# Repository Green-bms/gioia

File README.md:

# Gioia - glittering fashion
Electronic wearable device <br> 
<br> 

Youtube: https://youtu.be/MnyeiMZdmjQ?si=YpLxnYz4cA8ocs8j <br> 
Instructables: https://www.instructables.com/Gioia-Glittering-Fashion/ <br> 
Hackaday.io: https://hackaday.io/project/202226-gioia-glittering-fashion <br> 
Hackster.io: https://www.hackster.io/green-bms/gioia-glittering-fashion-81f5f8 <br> 
Purchase PCB here: <br> 
https://www.pcbway.com/project/shareproject/Gioia_glittering_fashion_21_monocrome_leds_caeb9192.html  <br>
https://www.pcbway.com/project/shareproject/Gioia_glittering_fashion_8_RGB_leds_abd15673.html <br>

## Description
"Gioia" in Italian means joy.<br> 
I wanted to call this project this way in the hope that it will bring joy and happiness to those who wear it.<br> 
This gadget of 3 cm of diametrer can contain a maximum of 24 single-color LEDs or 8 RGB LEDs.<br> 
The infinite animations, which also include letters and symbols, are managed by an Attiny85 microcontroller.<br> 

### The PCB
Gioia's PCBs are made by PCBway https://pcbway.com/g/kY6w10 <br>
 <br>
I chose this supplier because the quality of the PCB and the assembly of the components is of great quality.
The assistance is excellent and the delivery times are always respected <br>
 <br>

### Battery
The device is powered by a 30mAh LIR1632 rechargeable lithium battery. <br>
 <br> 
Charging is done via a micro USB connector and takes about 90 minutes from 0% to 100%
The device lasts for about 5 continuous hours

### Versions
The project is available in 2 versions:<br>

#### 21 monochrome leds:<br>
 <br> 
All the documentation to make it is available here: https://github.com/Green-bms/gioia/tree/master/21%20monochrome%20leds%20version

#### 8 RGB leds:<br>
 <br> 
Each LED can light up in one of these 7 colors: red, green, blue, yellow, fuchsia, aqua, white. <br>
All the documentation to make it is available here: https://github.com/Green-bms/gioia/tree/master/8%20RGB%20leds%20version

### Microcontroller
The device's LEDs are driven by an Attiny85 microcontroller and 3 74HC595 shift registers.<br> 
The LED animations that can compose various light games, texts and symbols, are programmed in the code to be loaded into the microcontroller<br> 
Programming the microcontroller is very simple: you need to power the device via USB and connect the 4 pins of the ISP programmer to the pads shown in the pictures below.<br> 

## Open source Development applications
The project was created using the following Open source applications:
- **KiCad** : to design pcb
- **Arduino IDE** : to design the code for Attiny85 microcontroller of device animations

## Warning
This project is not commercial. This project is for educational and technological purposes.
No warrenty is foreseen.
Green BMS assumes no responsibility for any errors or inaccuracies that may appear in any documentation or file or any software that may be provided.
The use of this project is done entirely at your own risk and responsibility.
The use of this project may not be compliant with local laws or regulations.

## License

This work is licensed under a **Creative Commons Attribution-ShareAlike 4.0 International License**.
https://creativecommons.org/licenses/by-sa/4.0/

### You are free to:

**Share** — copy and redistribute the material in any medium or format

**Adapt**  — remix, transform, and build upon the material
for any purpose, even commercially.
This license is acceptable for Free Cultural Works.
The licensor cannot revoke these freedoms as long as you follow the license terms.

### Under the following terms:

**Attribution** — You must give appropriate credit, provide a link to the license, and indicate if changes were made. You may do so in any reasonable manner, but not in any way that suggests the licensor endorses you or your use.

**ShareAlike** — If you remix, transform, or build upon the material, you must distribute your contributions under the same license as the original.

**No additional restrictions** — You may not apply legal terms or technological measures that legally restrict others from doing anything the license permits.

### Notices:
You do not have to comply with the license for elements of the material in the public domain or where your use is permitted by an applicable exception or limitation.
No warranties are given. The license may not give you all of the permissions necessary for your intended use. For example, other rights such as publicity, privacy, or moral rights may limit how you use the material.

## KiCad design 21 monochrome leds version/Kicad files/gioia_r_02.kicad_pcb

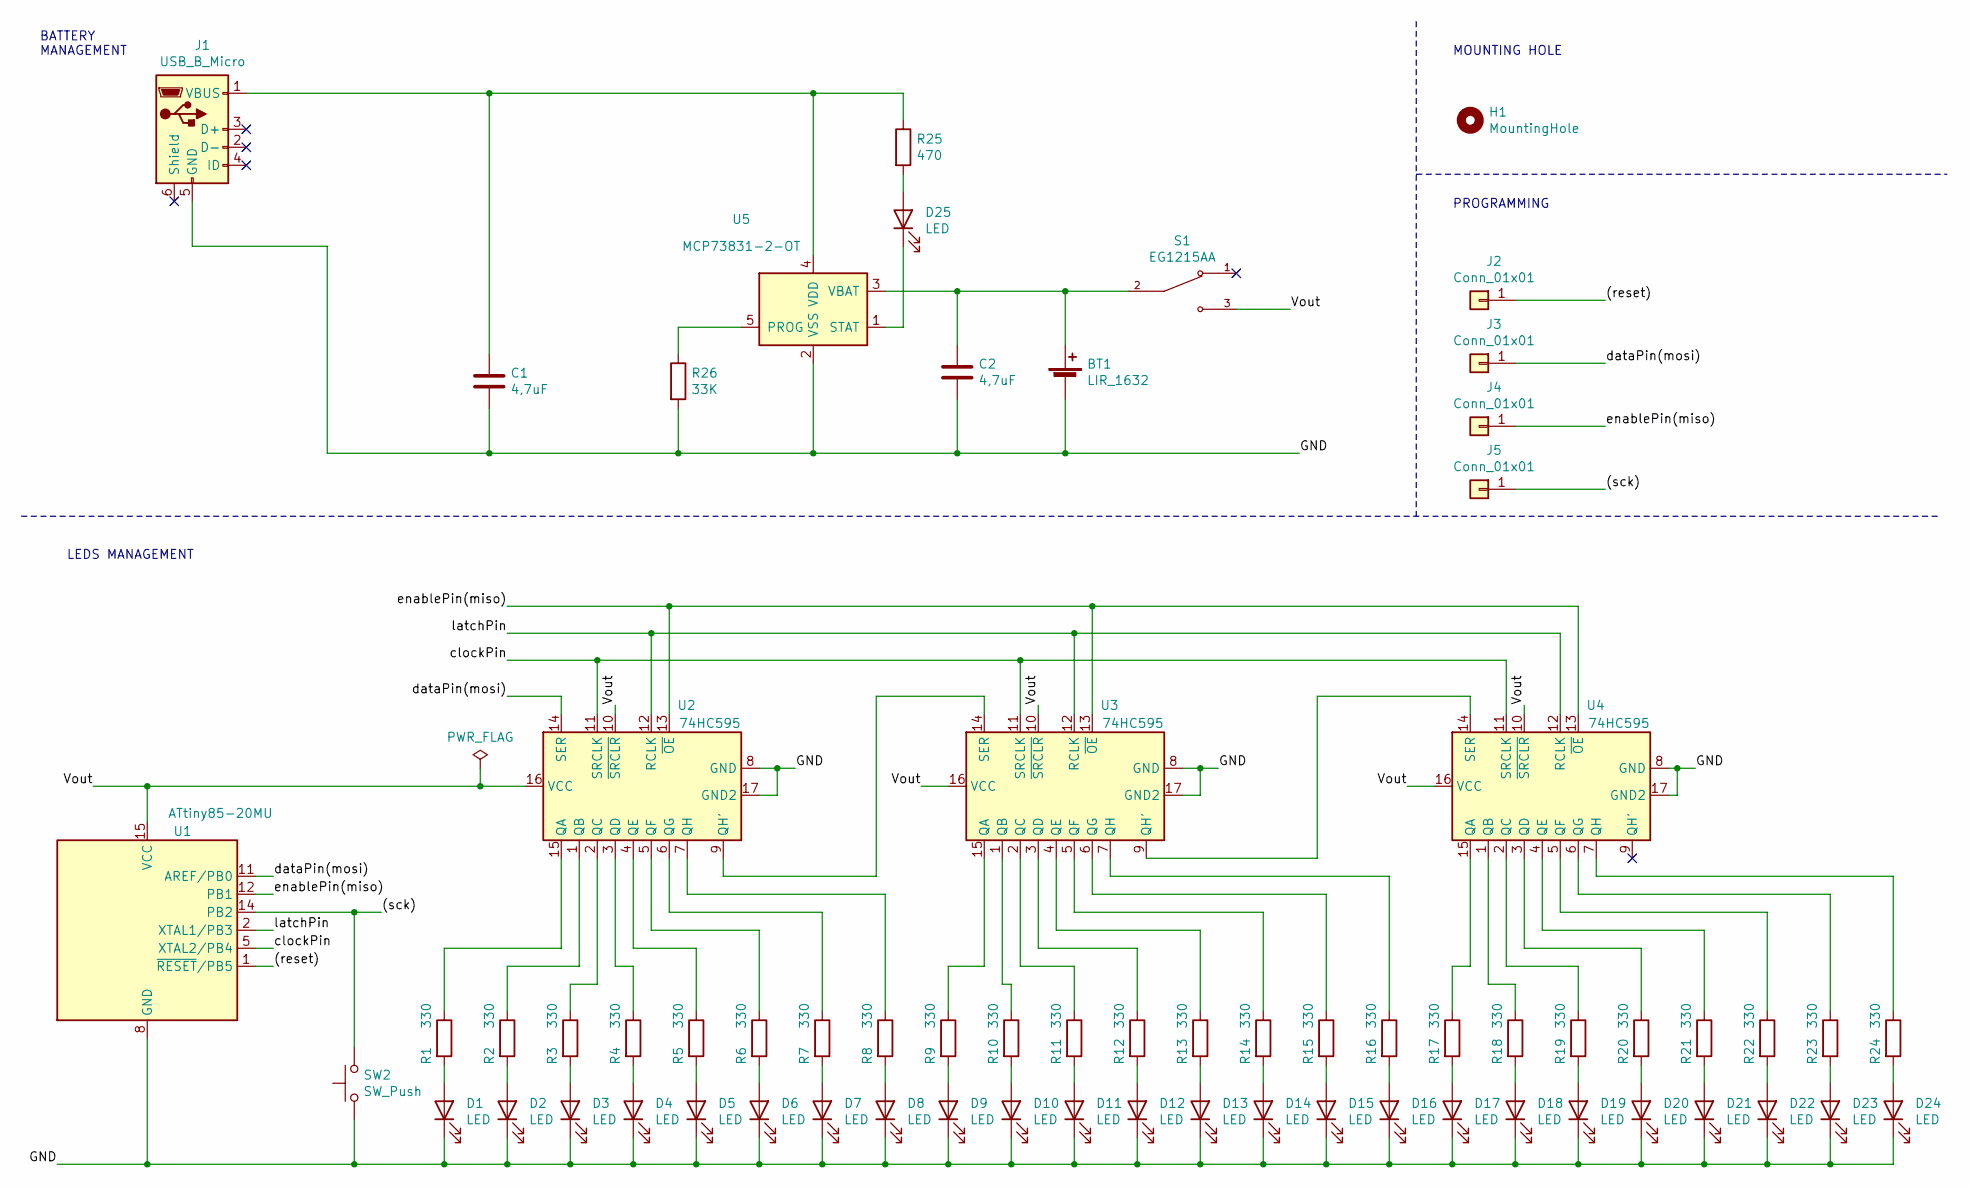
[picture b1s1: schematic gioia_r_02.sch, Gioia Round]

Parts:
BT1: LIR_1632; LIR1632_SMD
C1, C2: 4,7uF; C_0402_1005Metric
D1, D2, D3, D4, D5, D6, D7, D8, D9, D10, D11, D12, D13, D14, D15, D16, D17, D18, D19, D20, D21, D22, D23, D24: LED; LED_1206_3216Metric
D25: LED; LED_0402_1005Metric
H1: MountingHole; MountingHole_2.1mm
J1: USB_B_Micro; USB_Micro-B_Amphenol_10104110_Horizontal
J2, J3, J4, J5: Conn_01x01; TestPoint_THTPad_D1.0mm_Drill0.6mm
R1, R2, R3, R4, R5, R6, R7, R8, R9, R10, R11, R12, R13, R14, R15, R16, R17, R18, R19, R20, R21, R22, R23, R24: 330; R_0402_1005Metric
R25: 470; R_0402_1005Metric
R26: 33K; R_0402_1005Metric
S1: EG1215AA; SW_EG1215AA; PARTREV A
SW2: SW_Push; SW_SPST_B3U-3000P
U1: ATtiny85-20MU; QFN-20-1EP_4x4mm_P0.5mm_EP2.6x2.6mm
U2, U3, U4: 74HC595; DHVQFN16
U5: MCP73831-2-OT; SOT-23-5

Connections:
/(reset): J2.1, U1.1 (~RESET~/PB5)
/(sck): J5.1, SW2.2, U1.14 (PB2)
/GND: BT1.2 (-), C1.2, C2.2, D1.1 (K), D2.1 (K), D3.1 (K), D4.1 (K), D5.1 (K), D6.1 (K), D7.1 (K), D8.1 (K), D9.1 (K), D10.1 (K), D11.1 (K), D12.1 (K), D13.1 (K), D14.1 (K), D15.1 (K), D16.1 (K), D17.1 (K), D18.1 (K), D19.1 (K), D20.1 (K), D21.1 (K), D22.1 (K), D23.1 (K), D24.1 (K), J1.5 (GND), R26.2, SW2.1, U1.8 (GND), U1.21 (GND), U2.8 (GND), U2.17 (GND2), U3.8 (GND), U3.17 (GND2), U4.8 (GND), U4.17 (GND2), U5.2 (VSS)
/Vout: S1.3, U1.15 (VCC), U2.10 (~SRCLR), U2.16 (VCC), U3.10 (~SRCLR), U3.16 (VCC), U4.10 (~SRCLR), U4.16 (VCC)
/clockPin: U1.5 (XTAL2/PB4), U2.11 (SRCLK), U3.11 (SRCLK), U4.11 (SRCLK)
/dataPin(mosi): J3.1, U1.11 (AREF/PB0), U2.14 (SER)
/enablePin(miso): J4.1, U1.12 (PB1), U2.13 (~OE), U3.13 (~OE), U4.13 (~OE)
/latchPin: U1.2 (XTAL1/PB3), U2.12 (RCLK), U3.12 (RCLK), U4.12 (RCLK)
unnamed: BT1.1 (+), C2.1, S1.2, U5.3 (VBAT)
unnamed: C1.1, J1.1 (VBUS), R25.1, U5.4 (VDD)
unnamed: D1.2 (A), R1.2
unnamed: D2.2 (A), R2.2
unnamed: D3.2 (A), R3.2
unnamed: D4.2 (A), R4.2
unnamed: D5.2 (A), R5.2
unnamed: D6.2 (A), R6.2
unnamed: D7.2 (A), R7.2
unnamed: D8.2 (A), R8.2
unnamed: D9.2 (A), R9.2
unnamed: D10.2 (A), R10.2
unnamed: D11.2 (A), R11.2
unnamed: D12.2 (A), R12.2
unnamed: D13.2 (A), R13.2
unnamed: D14.2 (A), R14.2
unnamed: D15.2 (A), R15.2
unnamed: D16.2 (A), R16.2
unnamed: D17.2 (A), R17.2
unnamed: D18.2 (A), R18.2
unnamed: D19.2 (A), R19.2
unnamed: D20.2 (A), R20.2
unnamed: D21.2 (A), R21.2
unnamed: D22.2 (A), R22.2
unnamed: D23.2 (A), R23.2
unnamed: D24.2 (A), R24.2
unnamed: D25.1 (K), U5.1 (STAT)
unnamed: D25.2 (A), R25.2
unnamed: R1.1, U2.15 (QA)
unnamed: R2.1, U2.1 (QB)
unnamed: R3.1, U2.2 (QC)
unnamed: R4.1, U2.3 (QD)
unnamed: R5.1, U2.4 (QE)
unnamed: R6.1, U2.5 (QF)
unnamed: R7.1, U2.6 (QG)
unnamed: R8.1, U2.7 (QH)
unnamed: R9.1, U3.15 (QA)
unnamed: R10.1, U3.1 (QB)
unnamed: R11.1, U3.2 (QC)
unnamed: R12.1, U3.3 (QD)
unnamed: R13.1, U3.4 (QE)
unnamed: R14.1, U3.5 (QF)
unnamed: R15.1, U3.6 (QG)
unnamed: R16.1, U3.7 (QH)
unnamed: R17.1, U4.15 (QA)
unnamed: R18.1, U4.1 (QB)
unnamed: R19.1, U4.2 (QC)
unnamed: R20.1, U4.3 (QD)
unnamed: R21.1, U4.4 (QE)
unnamed: R22.1, U4.5 (QF)
unnamed: R23.1, U4.6 (QG)
unnamed: R24.1, U4.7 (QH)
unnamed: R26.1, U5.5 (PROG)
unnamed: U2.9 (QH'), U3.14 (SER)
unnamed: U3.9 (QH'), U4.14 (SER)

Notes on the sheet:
BATTERY MANAGEMENT
MOUNTING HOLE
LEDS MANAGEMENT
PROGRAMMING

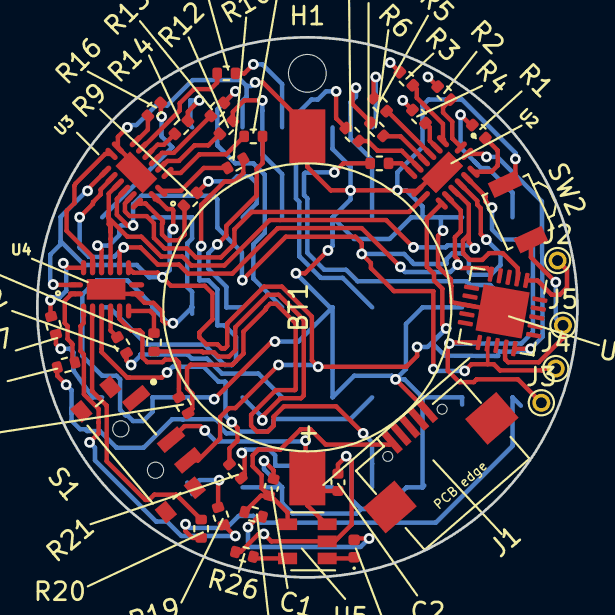
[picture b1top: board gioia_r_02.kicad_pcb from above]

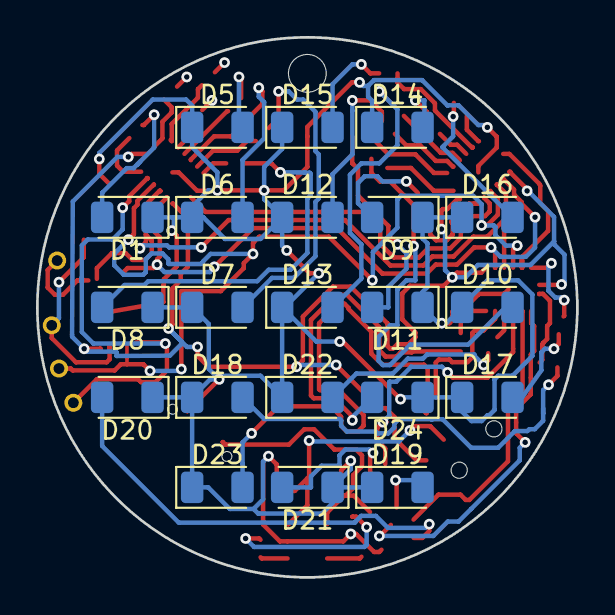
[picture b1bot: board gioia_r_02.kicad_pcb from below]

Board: 2 copper layers, 30.0 x 30.0 mm, 64 parts (21 on the bottom side), 60 nets.

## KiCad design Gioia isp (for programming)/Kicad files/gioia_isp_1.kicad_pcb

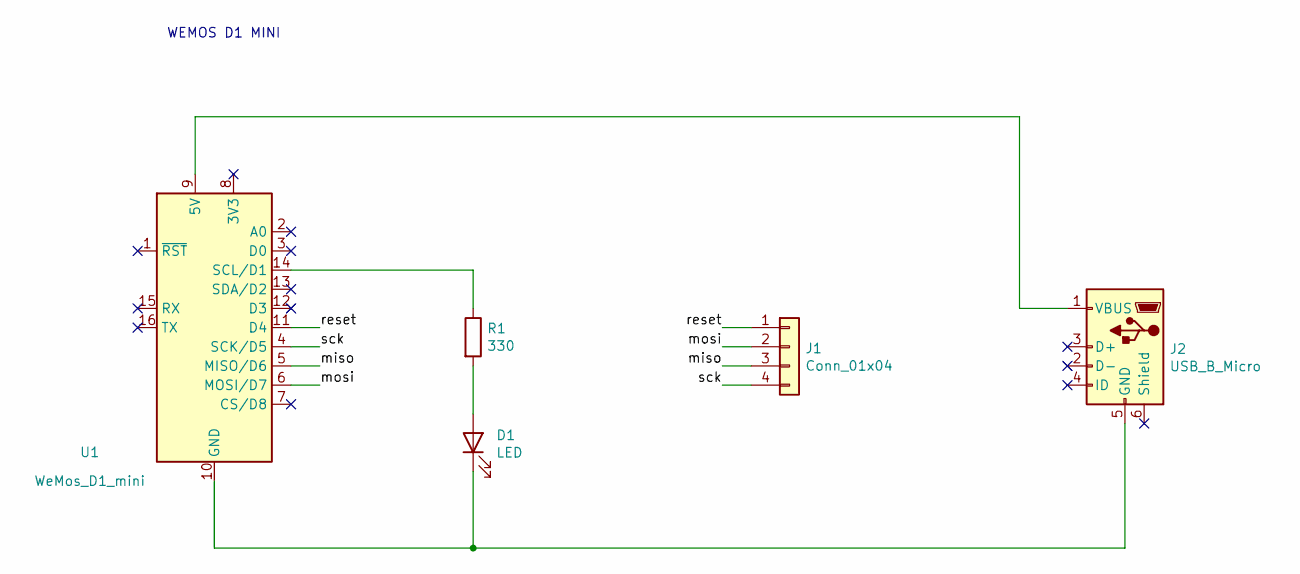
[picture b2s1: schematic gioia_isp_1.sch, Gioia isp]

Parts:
D1: LED; LED_D3.0mm
J1: Conn_01x04; PinSocket_1x04_P2.54mm_Vertical
J2: USB_B_Micro; USB_Micro-B_Amphenol_10104110_Horizontal
R1: 330; R_Axial_DIN0207_L6.3mm_D2.5mm_P2.54mm_Vertical
U1: WeMos_D1_mini; WEMOS_D1_mini_light

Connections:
/miso: J1.3, U1.5 (MISO/D6)
/mosi: J1.2, U1.6 (MOSI/D7)
/reset: J1.1, U1.11 (D4)
/sck: J1.4, U1.4 (SCK/D5)
unnamed: D1.1 (K), J2.5 (GND), U1.10 (GND)
unnamed: D1.2 (A), R1.2
unnamed: J2.1 (VBUS), U1.9 (5V)
unnamed: R1.1, U1.14 (SCL/D1)

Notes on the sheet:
WEMOS D1 MINI

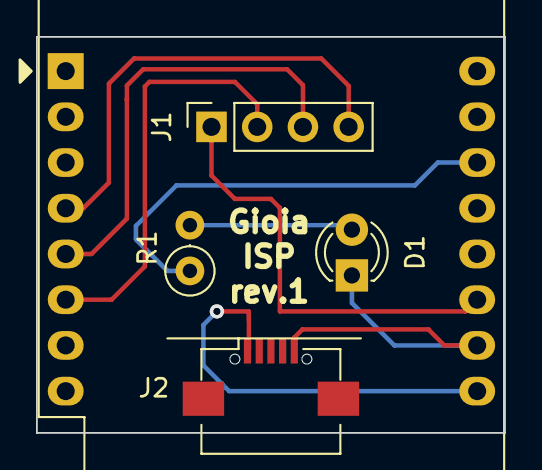
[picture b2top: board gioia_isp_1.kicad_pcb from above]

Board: 2 copper layers, 26.0 x 22.0 mm, 5 parts (0 on the bottom side), 8 nets.
